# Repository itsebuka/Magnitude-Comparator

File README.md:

# 🔲 4-Bit Magnitude Comparator & Display — PCB Design

> A hardware PCB module that compares two 4-bit binary numbers and visually indicates the result via three dedicated LED outputs. Built as part of the **EEE 312 (Digital Electronics) Capstone Project** at Pan Atlantic University.

---

## 📌 Overview

This module receives two 4-bit binary numbers (**A** and **B**) from an external register block, compares them using a **74LS85 TTL Magnitude Comparator IC**, and drives one of three LEDs to indicate the result:

| LED | Condition |
|-----|-----------|
| 🔴 LED 1 | A > B |
| 🟡 LED 2 | A = B |
| 🟢 LED 3 | A < B |

> ⚠️ By design, only **one LED is active at any given time** — the outputs are mutually exclusive.

This is a standalone comparator block intended to integrate into a larger multi-block digital logic system. Inputs A0–A3 and B0–B3 are brought in via an 8-pin header connector (J1), making it modular and system-compatible.

---

## 🧰 Bill of Materials (BOM)

| Ref | Component | Value / Part No. | Notes |
|-----|-----------|-----------------|-------|
| U1 | 4-bit TTL Magnitude Comparator | 74LS85 | DIP-16 package |
| D1, D2, D3 | LEDs | Standard 5mm | A>B, A=B, A<B indicators |
| R4, R5, R6 | Current-limiting resistors | 330Ω | One per LED |
| C1 | Decoupling capacitor | 100nF ceramic | Across VCC/GND, noise filtering |
| J1 | Input connector | 8-pin 2.54mm pitch header | A0–A3, B0–B3 inputs |
| — | Power supply | 5V TTL-compatible | — |

---

## 🔌 Pinout — J1 Input Connector

| Pin | Signal |
|-----|--------|
| 1 | A0 (LSB) |
| 2 | A1 |
| 3 | A2 |
| 4 | A3 (MSB) |
| 5 | B0 (LSB) |
| 6 | B1 |
| 7 | B2 |
| 8 | B3 (MSB) |

---

## 🛠 Tools Used

| Tool | Purpose |
|------|---------|
| **KiCAD 10.0** | Schematic capture & PCB layout |
| **GitHub Desktop** | Version control |

---

## 📁 Repository Structure

```
Magnitude-Comparator-main/
│
├── Comparator project.kicad_sch          # Main schematic file
├── Comparator project.kicad_pcb          # PCB layout file
├── Comparator project.kicad_pro          # KiCAD project file
│
├── Comparator project MAIN.kicad_sch     # Main (alternate) schematic
├── Comparator project PCB Schematic.kicad_pcb   # PCB schematic
├── Comparator project PCB Schematic.kicad_pro   # PCB project file
│
├── Comparator project-backups/           # Auto-saved KiCAD backups
│
├── report.txt                            # KiCAD symbol update log
└── README.md
```

---

## ⚙️ How to Open

1. Install [KiCAD 10.0](https://www.kicad.org/download/) or later.
2. Clone or download this repository.
3. Open `Comparator project.kicad_pro` in KiCAD.
4. The schematic and PCB layout will load automatically from within the project.

---

## 🔁 How It Works

The **74LS85** is a 4-bit magnitude comparator IC that takes two 4-bit inputs (A3–A0 and B3–B0) and three cascading inputs (A=B, A>B, A<B — tied to their respective logic levels for standalone use), and produces three active-high outputs:

- **OA>B** → HIGH when A is numerically greater than B
- **OA=B** → HIGH when A equals B  
- **OA<B** → HIGH when A is numerically less than B

Each output drives one LED through a 330Ω current-limiting resistor. The 100nF decoupling capacitor on the power rail suppresses switching noise from the TTL logic.

---

## 📝 Design Notes

- Power supply must be **5V TTL-compatible**. The 74LS85 operates between 4.75V and 5.25V.
- The cascading inputs (pins 2, 3, 4) are wired for **standalone operation**. For cascading multiple comparators to handle wider bit-widths, these need to be connected to the outputs of the lower-order comparator stage.
- This PCB is a **first revision** — trace routing and component placement may not be fully optimized. Improvements are planned in future iterations.

---

## 🔭 Future Improvements

- [ ] Add silkscreen labels for LED indicators (A>B, A=B, A<B) directly on the PCB
- [ ] Cascade to 8-bit comparison using two 74LS85 stages
- [ ] Add onboard power regulation (e.g. 7805) to accept a wider input voltage range
- [ ] Export Gerber files for PCB fabrication
- [ ] Add a ground plane pour for improved noise immunity

---

## 👤 Author

**Eleogu Chukwuebuka Joseph (Ebuka)**  
Electrical/Electronics Engineering Student  
Pan Atlantic University  
GitHub: [@itsebuka](https://github.com/itsebuka)  
Email: eleogujoseph007@gmail.com

---

> *"This marks my first real personal milestone project that I have ever done from scratch by myself. It's not perfect, but it is undoubtedly a step in the right direction."*

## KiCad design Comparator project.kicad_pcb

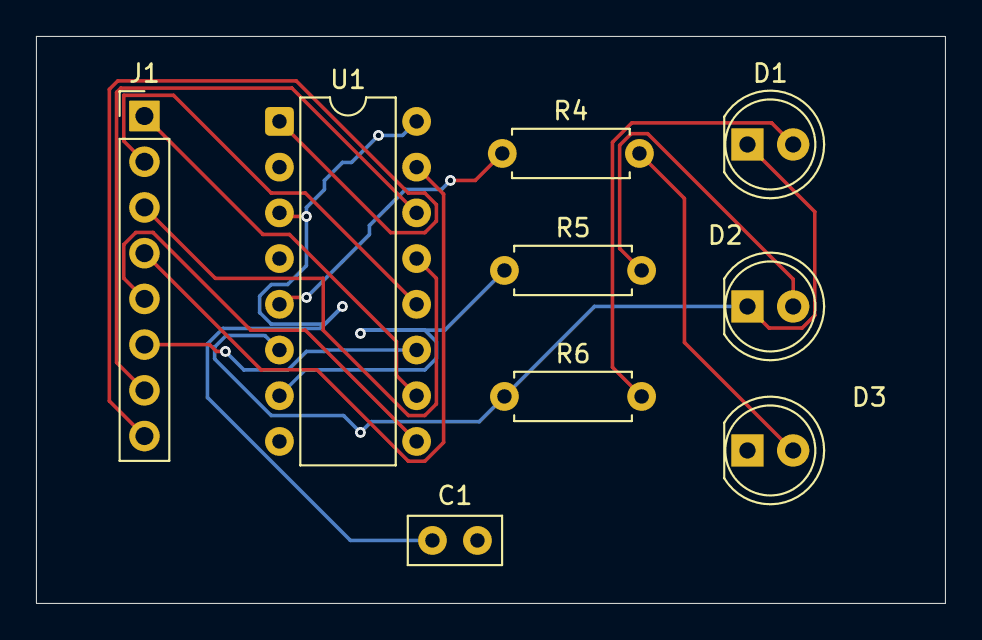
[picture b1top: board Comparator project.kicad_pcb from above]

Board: 2 copper layers, 50.5 x 31.5 mm, 9 parts (0 on the bottom side), 16 nets.

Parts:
C1: C; C_Disc_D5.0mm_W2.5mm_P2.50mm
D1, D2, D3: LED; LED_D5.0mm
J1: Conn_01x08; PinHeader_1x08_P2.54mm_Vertical
R4, R5, R6: R; R_Axial_DIN0207_L6.3mm_D2.5mm_P7.62mm_Horizontal
U1: 74LS85; DIP-16_W7.62mm

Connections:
+5V: C1.1, U1.3 (Ia=b), U1.16 (VCC)
GND: C1.2, D3.1 (K), U1.2 (Ia<b), U1.4 (Ia>b), U1.8 (GND)
unnamed: D1.2 (A), R6.2
unnamed: D2.2 (A), R5.2
unnamed: D3.2 (A), R4.2
unnamed: J1.1, U1.10 (A0)
unnamed: J1.2, U1.12 (A1)
unnamed: J1.3, U1.13 (A2)
unnamed: J1.4, U1.15 (A3)
unnamed: J1.5, U1.9 (B0)
unnamed: J1.6, U1.11 (B1)
unnamed: J1.7, U1.14 (B2)
unnamed: J1.8, U1.1 (B3)
unnamed: R5.1, U1.7 (Oa<b)
unnamed: D1.1 (K), D2.1 (K), R6.1, U1.6 (Oa=b)
unnamed: R4.1, U1.5 (Oa>b)

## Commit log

2026-05-13 My 4-Bit comparator
    This project takes two 4-bit binary inputs A and B, compares them using a 74LS85 IC, and displays the result (A>B, A=B, A<B) via three indicator LEDs.
2026-05-13 Add README with project overview and contact information
    Added detailed overview, design specifications, tools used, and personal reflections about the PCB design project.
2026-05-28 Revise README for clarity and additional information
    Updated README to enhance project overview and details.
